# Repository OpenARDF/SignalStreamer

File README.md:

# SignalStreamer
A simple, compact, effective 80m radio orienteering transmit antenna

SignalStreamer is an 80-meter-band radio-orienteering (ARDF) transmit antenna kit designed to operate in the Amateur Radio Service 3.5 MHz to 3.7 MHz frequency range. The antenna is the perfect complement to the SignalSlinger 80m transmitter. It even fits into an identical box!

The SignalStreamer project is 100% Open Source. All the KiCad hardware design documents are available for download from this GitHub repository.

User Manual: <a href="https://docs.google.com/document/d/1ixdft7eyVAQ5lvPSUMsNJx15NzzCWhzimSsPBIRxByI/edit?usp=sharing">Assembly & User Manual</a>.

A matching transmitter: <a href="https://github.com/OpenARDF/SignalSlinger">SignalSlinger</a>.

## Rev 1.2 dual-assembly prototype

The [KiCad 10 project](KiCad/SignalStreamer.kicad_pro) fits either a machine-placed SMD detector or a fully hand-built through-hole detector on one PCB. All 11 capacitors, 5 fixed resistors and 11 diodes have paired footprints. Both builds use the Rev 1.1 circuit, the same through-hole RV101 trimmer, L101 inductor, T101 transformer and J105 BNC, and the same machined Polycase enclosure. The [assembly guide](Docs/Assembly-1.2.md) links the two BOMs, placement and fabrication files, FreeCAD model, machining drawing and first-article checks. Earlier Gerbers and the earlier board STEP remain under `KiCad/`. Use `Manufacturing/1.2-prototype/` for this revision.

On macOS, double-click [Open SignalStreamer Design.command](Open%20SignalStreamer%20Design.command) in Finder to open the KiCad 10 project and the [FreeCAD enclosure](Mechanical/SignalStreamer-enclosure.FCStd) together. In the KiCad project tree, double-click `SignalStreamer.kicad_pcb` to review the layout or `SignalStreamer.kicad_sch` to review the circuit.

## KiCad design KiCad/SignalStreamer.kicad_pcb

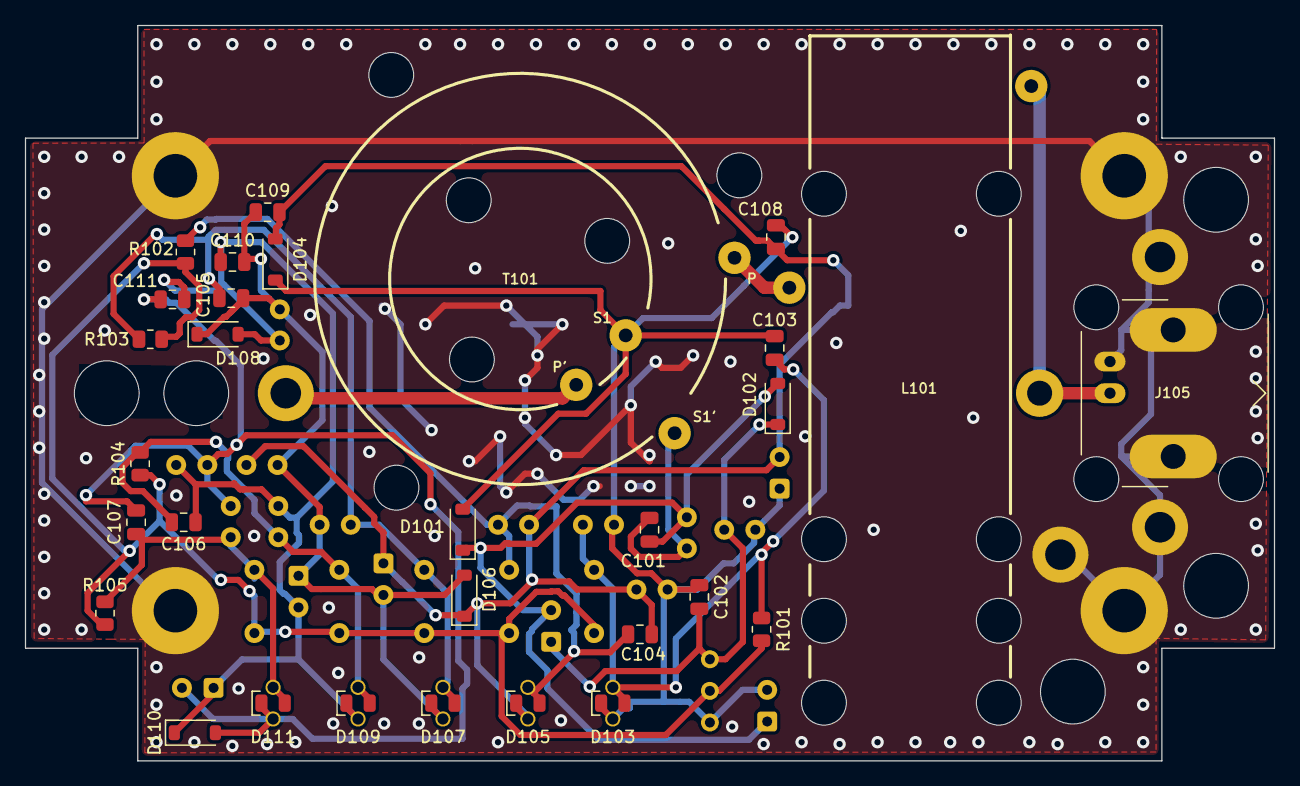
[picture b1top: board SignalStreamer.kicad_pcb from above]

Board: 2 copper layers, 100.3 x 59.1 mm, 71 parts (0 on the bottom side), 18 nets.

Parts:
C101, C102, C103, C104, C105, C106, C107, C108, C109, C110, C111: 470nF; C_0805_2012Metric
C201, C202, C203, C204, C205, C206, C207, C208, C209, C210, C211: 470nF; C_Rect_L4.0mm_W2.5mm_P2.50mm_BackSilk
D101, D102: 1N5711; D_SOD-123
D103, D105, D107, D109, D111: Red LED; LED_0805_2012Metric_Dual
D104, D106, D108, D110: 1N4148; D_SOD-123
D201, D202: 1N5711; D_DO-35_SOD27_P2.54mm_Vertical_CathodeUp_BackSilk
D203, D205, D207, D209, D211: WP7113ID; LED_D5mm_P2.54mm_Dual
D204, D206, D208, D210: 1N4148; D_DO-35_SOD27_P2.54mm_Vertical_CathodeUp_BackSilk
J101, J102, J103, J104: Conn_01x01; Wire_14AWG
J105: BNC; BNC_31-5431
L101: FB-31-4852; L_Lipstick_Tube_Variable
MH1, MH2, MH3, MH4: Chassis PCB boss; MountingHole_3.5mm_Pad
R101, R102, R103, R104, R105: 470; R_0805_2012Metric
R201, R202, R203, R204, R205: 470; R_Axial_DIN0207_L6.3mm_D2.5mm_P5.08mm_Vertical_BackSilk
RV101: 2k; Potentiometer_Bourns_3296W_Vertical_BackSilk
T101: Coupled_Inductors_2; Core_T130_2_windings_Horiz_TH
W1, W2, W3, W4, W5: Wire strain relief; Insulated_wire_relief

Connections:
/DET_RETURN: C102.2, C103.2, C108.2, C202.2, C203.2, C208.2, D101.2 (A), D103.1 (K), D104.1 (K), D201.2 (A), D203.1 (K), D204.1 (K), RV101.3, T101.1 (PM)
/LED_A1: C103.1, C203.1, D103.2 (A), D203.2 (A), R101.2, R201.2
/LED_A2: C104.1, C204.1, D105.2 (A), D205.2 (A), R102.2, R202.2
/LED_A3: C105.1, C205.1, D107.2 (A), D207.2 (A), R103.2, R203.2
/LED_A4: C106.1, C206.1, D109.2 (A), D209.2 (A), R104.2, R204.2
/LED_A5: C107.1, C207.1, D111.2 (A), D211.2 (A), R105.2, R205.2
/LED_DRIVE: R101.1, R102.1, R103.1, R104.1, R105.1, R201.1, R202.1, R203.1, R204.1, R205.1, RV101.2
/PUMP: C101.1, C201.1, D101.1 (K), D102.2 (A), D201.1 (K), D202.2 (A)
/RECTIFIED: C102.1, C202.1, D102.1 (K), D202.1 (K), RV101.1
/RF_SAMPLE: C101.2, C201.2, T101.2 (IN+)
/STEP_1: C104.2, C108.1, C109.2, C204.2, C208.1, C209.2, D104.2 (A), D105.1 (K), D106.1 (K), D204.2 (A), D205.1 (K), D206.1 (K)
/STEP_2: C105.2, C109.1, C110.2, C205.2, C209.1, C210.2, D106.2 (A), D107.1 (K), D108.1 (K), D206.2 (A), D207.1 (K), D208.1 (K)
/STEP_3: C106.2, C110.1, C111.2, C206.2, C210.1, C211.2, D108.2 (A), D109.1 (K), D110.1 (K), D208.2 (A), D209.1 (K), D210.1 (K)
/STEP_4: C107.2, C111.1, C207.2, C211.1, D110.2 (A), D111.1 (K), D210.2 (A), D211.1 (K)
GND: J102.1, J103.1, J104.1, J105.2, MH1.1, MH2.1, MH3.1, MH4.1
unnamed: J101.1, T101.3 (OUT1A)
unnamed: J105.1, L101.2
unnamed: L101.1, T101.4 (OUT1B)

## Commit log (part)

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2026-01-01 Create Schematic.pdf
    Added schematic PDF
2026-01-03 Enhance README with detailed SignalStreamer description
    Expanded the description of the SignalStreamer antenna kit, including its compatibility with the SignalSlinger transmitter and open-source status.
2026-01-03 Add user manual note and link to SignalSlinger
    Updated README to include user manual information and link to SignalSlinger.
2026-01-03 Dev
    Schematic and board updates
2026-01-03 Ver X1.0
    Copied latest changes from backup project
2026-01-04 Development
    Updates
2026-01-04 Add image to README for SignalStreamer
    Added an image to the README for better visualization.
2026-01-04 Fix hyphenation in SignalStreamer description
    Corrected hyphenation in the description of SignalStreamer.
2026-01-04 Correct image link for SignalStreamer PCB
    Fixed image link formatting in README.md
2026-01-04 Rename Image
    For Readme
2026-01-04 Fix image path in README.md
2026-01-04 Fix image link formatting in README.md
2026-01-05 Development
    PCB Updates
2026-01-09 Ver 1.0
    Redesign of LED tuning indicator. All gerbers updated.
2026-01-10 PCB Updates
    Corrects a problem with horizontal radials connection to coax ground
2026-01-10 PCB
    Minor changes to improve clearances
2026-01-11 PCB
    Minor PCB tweaks
    Removes all DRC warnings
2026-01-24 Update user manual link in README
    Updated user manual link and removed placeholder text.
2026-01-26 Cleanup
    .gitignore update
    Removed .DS_Store files
    Removed old .html file
2026-02-02 Beautify Schematic
    Minor edits to schematic diagram component positions. No changes functionally.
